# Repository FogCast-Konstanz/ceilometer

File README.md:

# Fogcast ceilometer

Fogcast is an experimental laser ceilometer intended to measure atmospheric
backscatter and, eventually, cloud-base height. This repository contains the
instrument electronics and mechanical designs, Pico 2 firmware, board bring-up
interface, and Raspberry Pi acquisition and dashboard software.

The instrument uses pseudo-randomly modulated continuous-wave lidar (PRN-CW).
A laser transmits a repeating binary sequence. A silicon photomultiplier (SiPM)
receiver detects returned photons, and correlation with the transmitted sequence
produces a backscatter profile versus range.

## Project status

The project currently supports board commissioning, receiver characterization,
PRN acquisition, raw-data recording and range-profile display. It is a research
prototype: calibrated atmospheric ranging and automatic cloud-base detection
have not been established. Displayed profiles require timing, optical and
calibration validation before they can be interpreted as qualified measurements.

The firmware currently operates at **500 MHz with a requested 1.5 V core supply**,
above the Pico 2's rated clock. This configuration has been used in bench tests;
stability must be checked on each instrument. See the
[clock and watchdog notes](docs/bringup/operating-clock.md) for evidence and limits.

## Instrument architecture

- **Pico 2 / RP2350:** generates PRN modulation, counts receiver pulses, captures
  counter snapshots through DMA, accumulates histograms, and controls peripherals.
- **Transmitter:** laser-current DAC and driver, plus a TEC regulated from a
  DS18B20 laser-temperature sensor.
- **Receiver:** SiPM bias control, receiver-temperature feedback and an adjustable
  comparator threshold. Bias targets track temperature and are limited to 50 V;
  this software limit is not a measured-voltage hardware clamp.
- **Raspberry Pi:** supervises measurements over USB CDC, records raw histograms,
  calculates correlation profiles and serves the instrument dashboard.

Acquisition runs on one Pico core in finite bursts. A common hardware event
starts transmission and receiver sampling. Startup periods are discarded after
each restart, and sensor servicing occurs between bursts. The nominal one-second
integration refers to accepted exposure; elapsed time is longer because of
warmup and processing gaps. Both are recorded separately.

See [acquisition architecture](docs/architecture/continuous-acquisition.md) and
[USB protocol](interfaces/usb-protocol.md) for the implementation details.

## Explore without hardware

Requirements: Python 3.10 or newer. Run these commands from the repository root:

```sh
python -m venv .venv
# Linux / Raspberry Pi:
. .venv/bin/activate
# Windows PowerShell alternative: .venv\Scripts\Activate.ps1
python -m pip install -e software/instrument
ceilometer-dashboard --demo --http-port 8081
```

Open **http://127.0.0.1:8081/**. Demo mode uses simulated data and does not open
USB or control physical outputs.

If you need the binary CAD, print projects or other large design assets, install
Git LFS and run `git lfs pull` after cloning.

## Connect an instrument

1. Assemble and inspect the hardware against the
   [electronics sources](hardware/electronics/README.md). Review the
   [bring-up documentation](docs/bringup) and [laser safety material](docs/safety)
   before applying power or commissioning optical output.
2. Build and load the Pico firmware as described below. USB powers the Pico;
   the instrument's other circuits require their designed external supplies.
3. Open [software/bringup/index.html](software/bringup/index.html) directly in
   desktop Chrome or Edge. Connect through Web Serial to inspect sensors,
   configure parameters and commission each functional block. Confirm wiring,
   TEC polarity, temperature feedback, DAC limits and board-specific calibration.
4. Disconnect the bring-up GUI before starting the Pi application. Only one
   program should own the instrument's USB connection.
5. Start the instrument dashboard in the Python environment:

```sh
ceilometer-dashboard auto --http-port 8080 --output measurements
```

Open **http://127.0.0.1:8080/**. Automatic discovery selects only USB manufacturer
`Fogcast`, product `Fogcast Ceilometer`, with the expected Pico VID/PID. Other
Picos are ignored; multiple matching ceilometers require an explicit device
path. Firmware 0.6.4 or newer supplies this USB identity.

The application starts **disabled**. Select a measurement mode and press
**Enable instrument** explicitly. **Disable for servicing** requests shutdown
and reports whether the board has acknowledged the laser, bias and TEC off.
External supplies remain powered. Temperature, driver-fault, watchdog and USB
lease interlocks remain active; reconnecting does not resume measurement.

For access from another computer on a trusted network or VPN:

```sh
export CEILOMETER_WEB_TOKEN="$(python -c 'import secrets; print(secrets.token_urlsafe(32))')"
ceilometer-dashboard auto --listen 0.0.0.0 --http-port 8080 --output measurements
```

Open `http://<pi-address>:8080/` and enter the token. Network binding requires a
token of at least 24 characters. The supplied server uses HTTP; use an HTTPS
reverse proxy where transport encryption is required. Keep tokens and local
configuration outside Git.

## Build firmware and run checks

Firmware requirements: Pico SDK **2.3.0**, a compatible Arm GNU toolchain, CMake
and a supported build tool. Set the SDK path for your machine:

```sh
cmake -S firmware/pico2 -B build/firmware -DPICO_BOARD=pico2 -DPICO_SDK_PATH=/path/to/pico-sdk
cmake --build build/firmware
```

The output is `build/firmware/ceilometer.uf2`. To load it manually, hold BOOTSEL
while connecting the Pico and copy the UF2 to its bootloader drive. Select the
intended board carefully when several Picos are connected.

Power-driver build flags default **OFF**. Commissioned hardware requires the
appropriate `CEIL_ENABLE_LASER`, `CEIL_ENABLE_BIAS` and `CEIL_ENABLE_TEC` options,
as well as a calibrated `CEIL_BIAS_MAX_CODE`. Build permission alone does not
turn outputs on. Do not reuse another board's DAC calibration or limits without
verification; see [SiPM bias control](docs/bringup/sipm-bias.md) and
[temperature control](docs/bringup/temperature-control.md).

Portable regression checks require a native C compiler; install the instrument
Python dependencies first. Node.js 22 or newer enables the GUI protocol checks.

```sh
cmake -S firmware/pico2 -B build/host -DCEIL_HOST_TESTS=ON
cmake --build build/host
ctest --test-dir build/host --output-on-failure
python scripts/check_design_sources.py
```

After editing the bring-up GUI, regenerate its direct-open bundle with
`python software/bringup/build_bundle.py`. After changing firmware parameter or
telemetry inventories, first run `python software/bringup/update_metadata.py`.

## Repository guide

| Directory | Contents |
|---|---|
| [firmware/pico2](firmware/pico2) | C/PIO firmware, peripheral drivers and firmware tests |
| [software/bringup](software/bringup) | Direct-open HTML/Web Serial commissioning GUI |
| [software/instrument](software/instrument) | Python package, recorder, processing and Pi dashboard |
| [hardware/electronics](hardware/electronics) | KiCad projects, custom libraries and LTspice simulations |
| [hardware/mechanical](hardware/mechanical) | CAD exchange files, meshes, drawings, print projects and studies |
| [interfaces](interfaces) | USB protocol and recorded-data format |
| [analysis](analysis) | Bench datasets, calibration evidence and plotting scripts |
| [docs](docs) | Architecture, bring-up, operation and safety documentation |
| [deploy](deploy) | Pi service templates, release packaging, updates and rollback |

Live measurements and generated build outputs are not versioned. Small recorded
bench datasets are retained as engineering evidence; see the
[measurement format](interfaces/measurement-format.md) for data interpretation.

## Deployment

After building the firmware, create a checksummed runtime release:

```sh
python deploy/releases/package_release.py --output build/ceilometer-release.tar.gz
```

The archive contains the Pi application, deployment tools, interface documents
and UF2. It excludes CAD, credentials and live measurements. Service templates
are under `deploy/raspberry-pi/`; install/update tools are under `deploy/releases/`.
Automated updates require an explicitly configured Git repository and target
Pico serial number. Updates are applied only while outputs are confirmed off,
and the service restarts disabled. Hardware-only commits do not trigger the
firmware deployment workflow.

### Pi-initiated continuous deployment

GitHub Actions builds and tests a release, then publishes it to the repository's
`deploy` branch. **GitHub never connects to the Raspberry Pi.** A systemd timer
on the Pi initiates an outbound Git fetch every five minutes (with up to 30 s
jitter), starting about two minutes after boot. No inbound port, webhook,
public Pi address or university firewall exception is needed. The Pi needs
outbound HTTPS access to the Git server; configure its proxy if required.

After provisioning the instrument release under `/opt/ceilometer-firmware`,
install and configure the poller on the Pi:

```sh
sudo install -d -m 0750 /etc/ceilometer
sudo install -m 0600 /opt/ceilometer-firmware/deploy/raspberry-pi/cd.env.example /etc/ceilometer/cd.env
sudoedit /etc/ceilometer/cd.env
# Set the HTTPS repository URL, refs/heads/deploy and the target Pico USB serial.
sudo install -m 0644 /opt/ceilometer-firmware/deploy/raspberry-pi/ceilometer-update.service /etc/systemd/system/
sudo install -m 0644 /opt/ceilometer-firmware/deploy/raspberry-pi/ceilometer-update.timer /etc/systemd/system/
sudo systemctl daemon-reload
sudo systemctl enable --now ceilometer-update.timer
```

For a private repository, configure read-only Git credentials on the Pi for the
root-run updater. Do not embed credentials in the URL or commit them. GitHub
Actions needs permission to publish the deployment branch, but no Pi credentials.

```sh
systemctl list-timers ceilometer-update.timer
journalctl -u ceilometer-update.service -n 50
# Trigger an immediate check:
sudo systemctl start ceilometer-update.service
```

While measuring, or when shutdown cannot be confirmed, the updater defers the
update until a later poll. Network outages leave the installed release running;
the next scheduled poll retries. The installer verifies release hashes, targets
the configured Pico, checks the restarted service and attempts rollback on failure.
Neither polling nor an update automatically enables measurements. An initial
local installation is required before polling can update the Pi itself.

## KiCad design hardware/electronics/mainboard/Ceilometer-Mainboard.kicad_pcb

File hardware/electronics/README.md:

# Electronics sources

`mainboard` preserves the complete KiCad project, A/B board variants, custom
symbols/footprints, 3D models and project-local library tables. No board variant
was silently selected or deleted. `simulations` contains LTspice source studies.
`reference` contains historical firmware-review netlist/hash exports; the KiCad
sources are authoritative and those exports may describe earlier revisions.

`history/kicad-local-history.bundle` preserves all Git refs from KiCad local
history. Inspect separately with `git clone <bundle> <temporary-directory>`;
do not unpack it as a nested live repository. Automatic backups, lock files,
local editor preferences and cached Python files are excluded from the import.

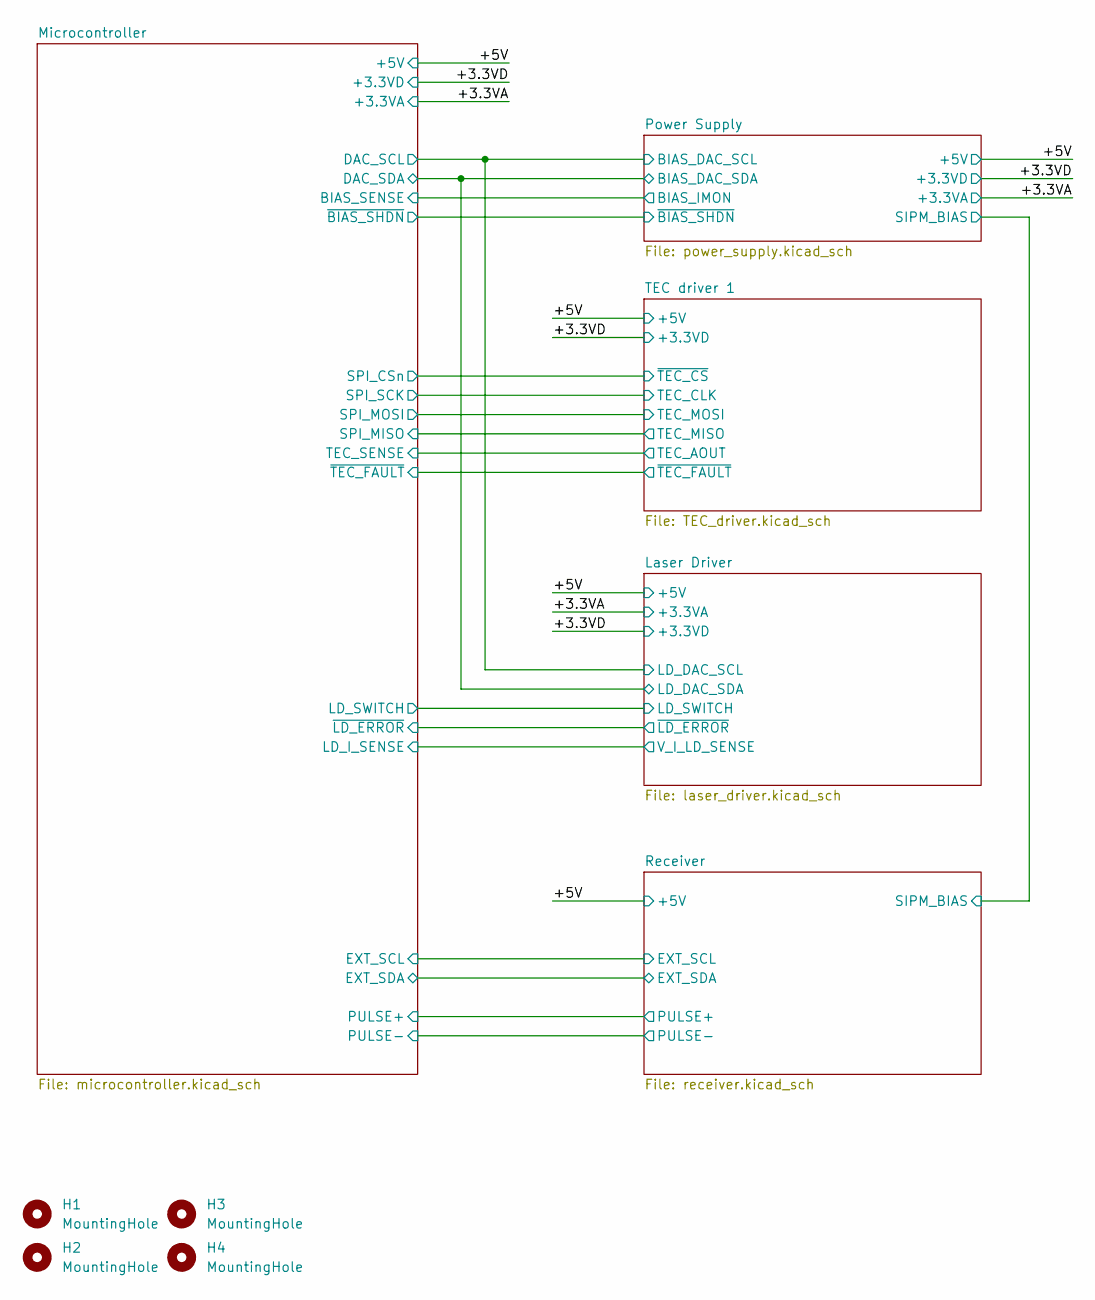
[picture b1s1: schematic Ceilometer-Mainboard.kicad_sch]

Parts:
H1, H2, H3, H4: MountingHole; MountingHole_2.5mm

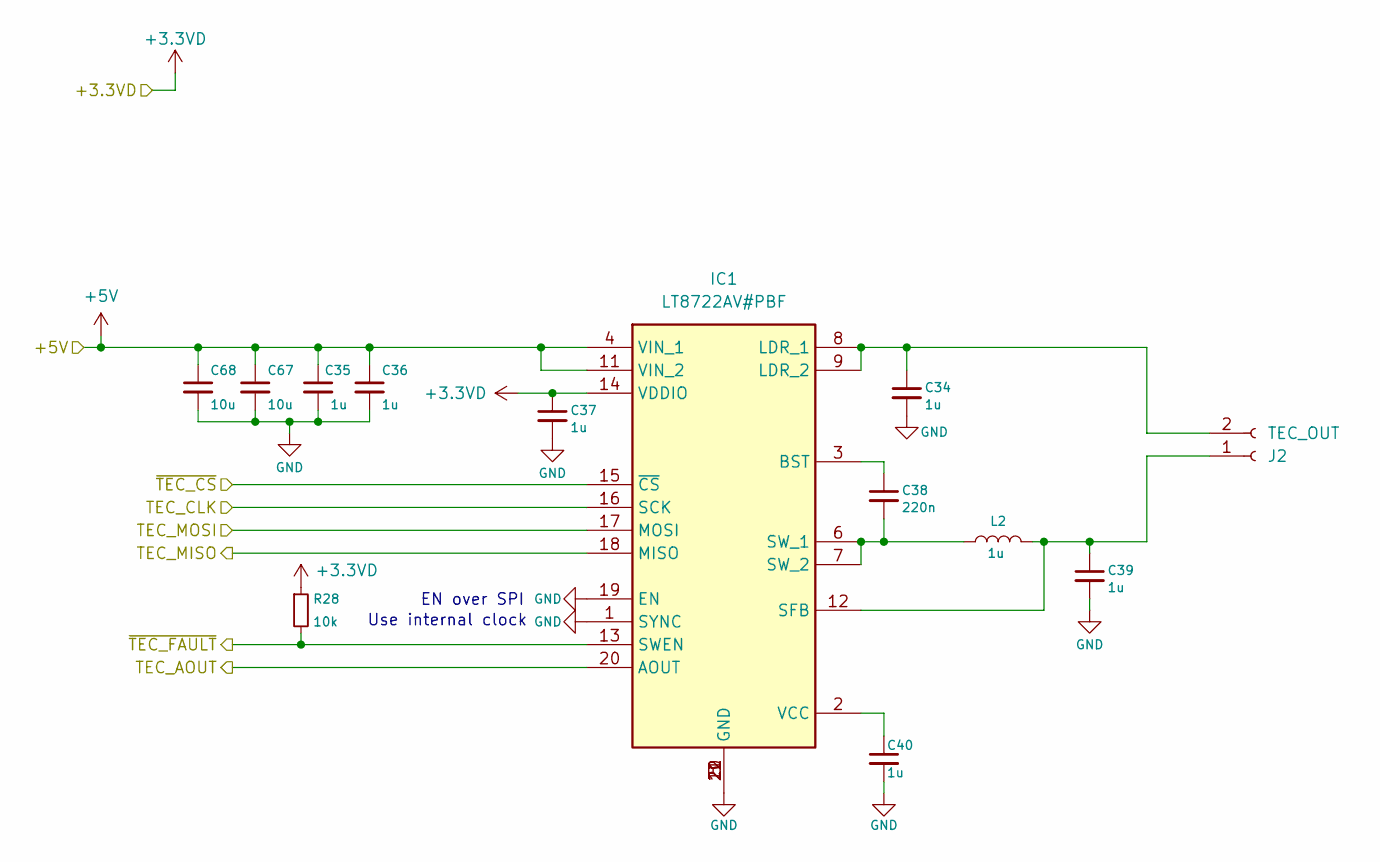
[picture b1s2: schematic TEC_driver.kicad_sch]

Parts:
C34, C35, C36, C37, C39, C40: 1u; C_0402_1005Metric; Voltage 35V; MPN C1005X5R1V105K050BE
C38: 220n; C_0402_1005Metric; Voltage 63V; MPN GRM155R61J224ME01J
C67, C68: 10u; C_0805_2012Metric; Voltage 50V; PartNumber GRM21BR61H106KE43K
IC1: LT8722AV#PBF; LT8722AVPBF; Mouser Part Number 584-LT8722AVPBF
J2: TEC_OUT; Molex_Pico-EZmate_78171-0002_1x02-1MP_P1.20mm_Vertical
L2: 1u; L_Wurth_WE-PMFI-252012; MPN 74479325207210
R28: 10k; R_0402_1005Metric; MPN ERA-2AEB103X

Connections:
+3.3VD: C37.1, IC1.14 (VDDIO), R28.1; also elsewhere on the board
+5V: C35.1, C36.1, C67.1, C68.1, IC1.4 (VIN_1), IC1.11 (VIN_2); also elsewhere on the board
/Microcontroller/SPI_CSn: IC1.15 (~CS); also elsewhere on the board
/Microcontroller/SPI_MISO: IC1.18 (MISO); also elsewhere on the board
/Microcontroller/SPI_MOSI: IC1.17 (MOSI); also elsewhere on the board
/Microcontroller/SPI_SCK: IC1.16 (SCK); also elsewhere on the board
/Microcontroller/TEC_SENSE: IC1.20 (AOUT); also elsewhere on the board
/Microcontroller/~TEC_FAULT: IC1.13 (SWEN), R28.2; also elsewhere on the board
GND: C34.2, C35.2, C36.2, C37.2, C39.2, C40.2, C67.2, C68.2, IC1.1 (SYNC), IC1.5 (GND), IC1.10 (GND), IC1.19 (EN), IC1.21 (GND), IC1.22 (GND); also elsewhere on the board
unnamed: C38.1, IC1.3 (BST)
unnamed: C34.1, IC1.8 (LDR_1), IC1.9 (LDR_2), J2.2
unnamed: C39.1, IC1.12 (SFB), J2.1, L2.2
unnamed: C38.2, IC1.6 (SW_1), IC1.7 (SW_2), L2.1
unnamed: C40.1, IC1.2 (VCC)

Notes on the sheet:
EN over SPI
Use internal clock

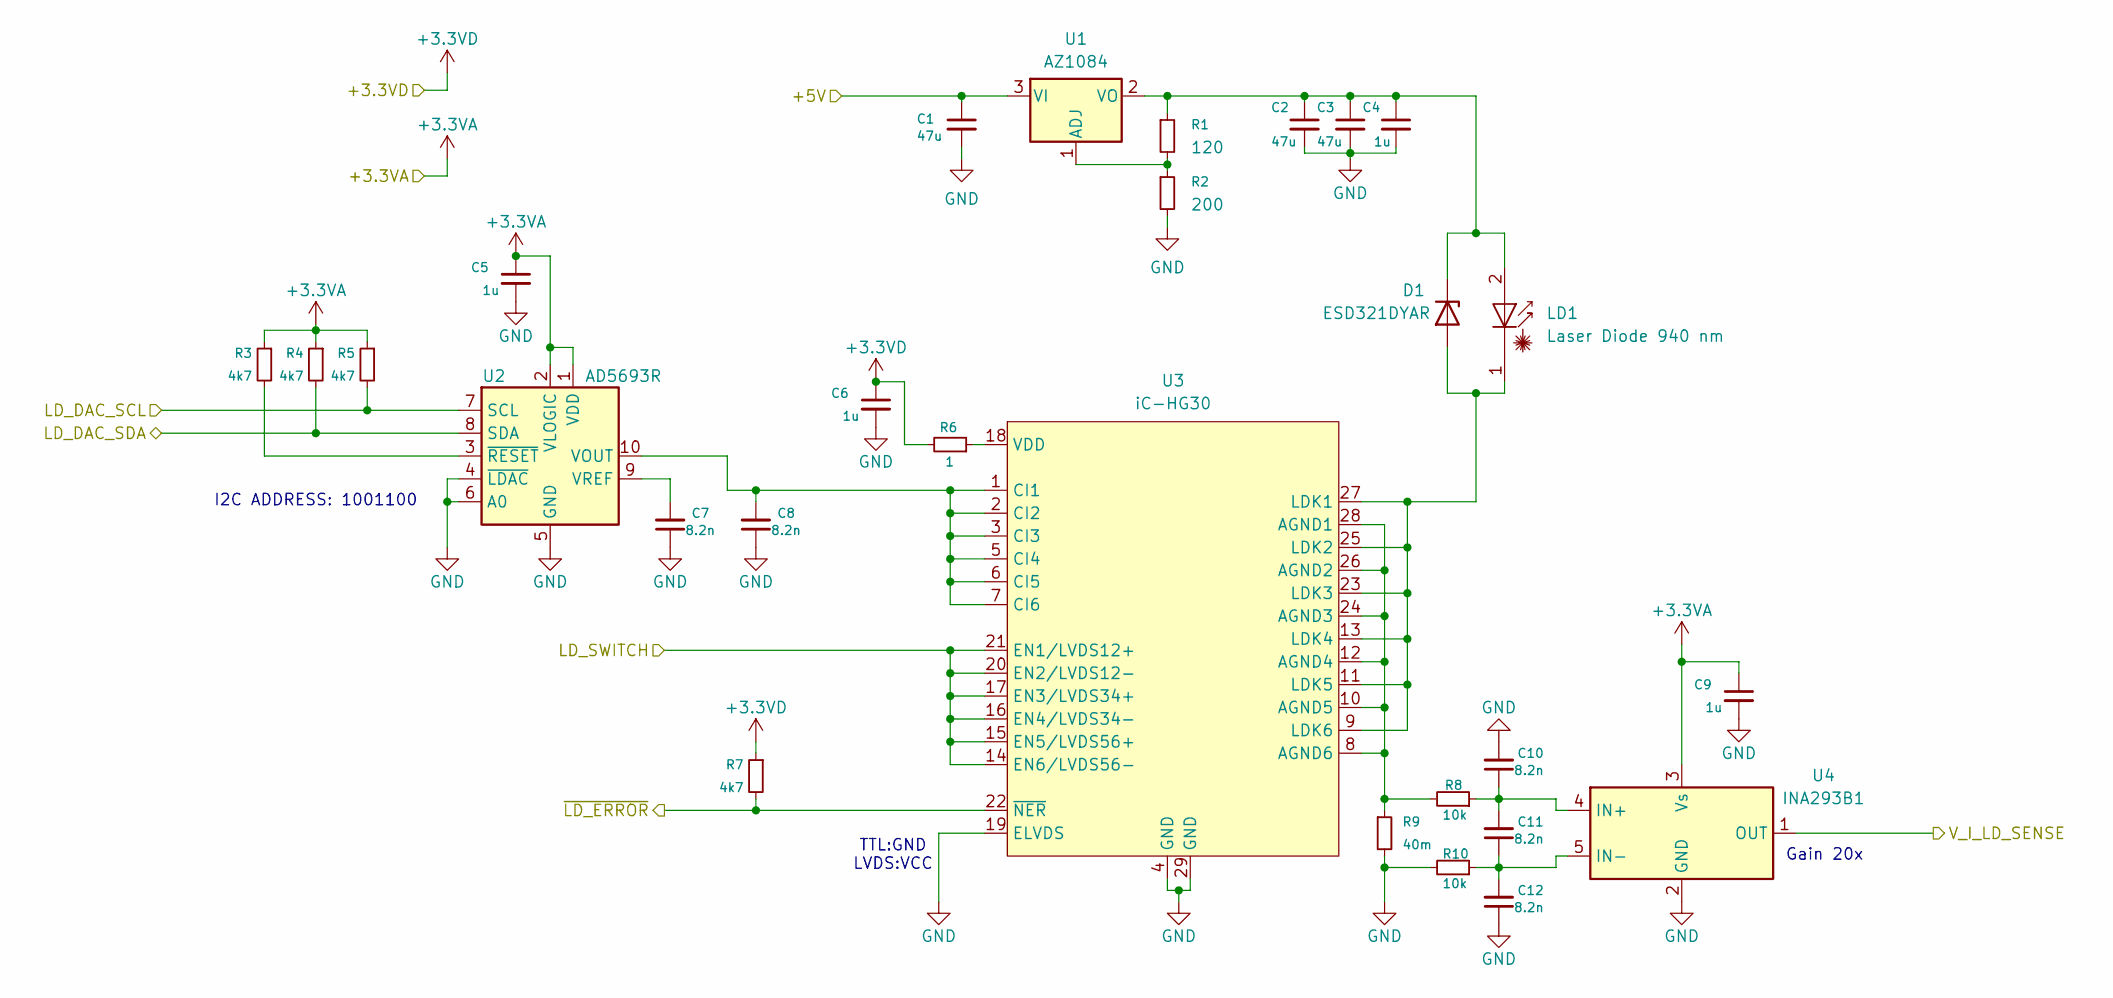
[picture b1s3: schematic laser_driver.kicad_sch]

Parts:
C1, C2, C3: 47u; C_0805_2012Metric; Voltage 10V; MPN LMK212BBJ476MG-T
C4, C5, C6, C9: 1u; C_0402_1005Metric; Voltage 35V; MPN C1005X5R1V105K050BE
C7, C8, C10, C11, C12: 8.2n; C_0402_1005Metric; Voltage 50V; MPN GRM1555C1H822JE01D
D1: ESD321DYAR; D_SOD-523; MPN ESD321DYAR
LD1: Laser Diode 940 nm; Molex_Pico-EZmate_78171-0002_1x02-1MP_P1.20mm_Vertical; MPN 781710002
R1: 120; R_0402_1005Metric; MPN ERA-2AEB121X
R2: 200; R_0402_1005Metric; MPN ERA-2AED201X
R3, R4, R5, R7: 4k7; R_0402_1005Metric; MPN ERA-2AED472X
R6: 1; R_0402_1005Metric; MPN CRCW04021R00FKED
R8, R10: 10k; R_0402_1005Metric; MPN ERA-2AEB103X
R9: 40m; R_0603_1608Metric; MPN PE0603DRF570R04L
U1: AZ1084; TO-263-2; MPN AZ1084CD-ADJTRG1
U2: AD5693R; MSOP-10_3x3mm_P0.5mm; MPN AD5693RARMZ-RL7
U3: iC-HG30; QFN-28-1EP_5x5mm_P0.5mm_EP3.1x3.15mm_ThermalVias; MPN iC-HG30
U4: INA293B1; SOT-23-5; MPN INA293B1IDBVR

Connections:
+3.3VA: C5.1, C9.1, R3.1, R4.1, R5.1, U2.1 (VDD), U2.2 (VLOGIC), U4.3 (Vs); also elsewhere on the board
+3.3VD: C6.1, R6.2, R7.1; also elsewhere on the board
+5V: C1.1, U1.3 (VI); also elsewhere on the board
/Laser Driver/LD_DAC_SCL: R5.2, U2.7 (SCL); also elsewhere on the board
/Laser Driver/LD_DAC_SDA: R4.2, U2.8 (SDA); also elsewhere on the board
/Laser Driver/LD_SWITCH: U3.14 (EN6/LVDS56-), U3.15 (EN5/LVDS56+), U3.16 (EN4/LVDS34-), U3.17 (EN3/LVDS34+), U3.20 (EN2/LVDS12-), U3.21 (EN1/LVDS12+); also elsewhere on the board
/Laser Driver/V_I_LD_SENSE: U4.1 (OUT); also elsewhere on the board
/Laser Driver/~LD_ERROR: R7.2, U3.22 (~NER); also elsewhere on the board
GND: C1.2, C2.2, C3.2, C4.2, C5.2, C6.2, C7.1, C8.1, C9.2, C10.2, C12.1, R2.2, R9.2, R10.2, U2.4 (~LDAC), U2.5 (GND), U2.6 (A0), U3.4 (GND), U3.19 (ELVDS), U3.29 (GND), U4.2 (GND); also elsewhere on the board
unnamed: D1.2 (A), LD1.1 (K), U3.9 (LDK6), U3.11 (LDK5), U3.13 (LDK4), U3.23 (LDK3), U3.25 (LDK2), U3.27 (LDK1)
unnamed: C2.1, C3.1, C4.1, D1.1 (K), LD1.2 (A), R1.1, U1.2 (VO)
unnamed: R1.2, R2.1, U1.1 (ADJ)
unnamed: C8.2, U2.10 (VOUT), U3.1 (CI1), U3.2 (CI2), U3.3 (CI3), U3.5 (CI4), U3.6 (CI5), U3.7 (CI6)
unnamed: C7.2, U2.9 (VREF)
unnamed: R3.2, U2.3 (~RESET)
unnamed: R8.2, R9.1, U3.8 (AGND6), U3.10 (AGND5), U3.12 (AGND4), U3.24 (AGND3), U3.26 (AGND2), U3.28 (AGND1)
unnamed: R6.1, U3.18 (VDD)
unnamed: C10.1, C11.2, R8.1, U4.4 (IN+)
unnamed: C11.1, C12.2, R10.1, U4.5 (IN-)

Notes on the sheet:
I2C ADDRESS: 1001100
TTL:GND LVDS:VCC
Gain 20x

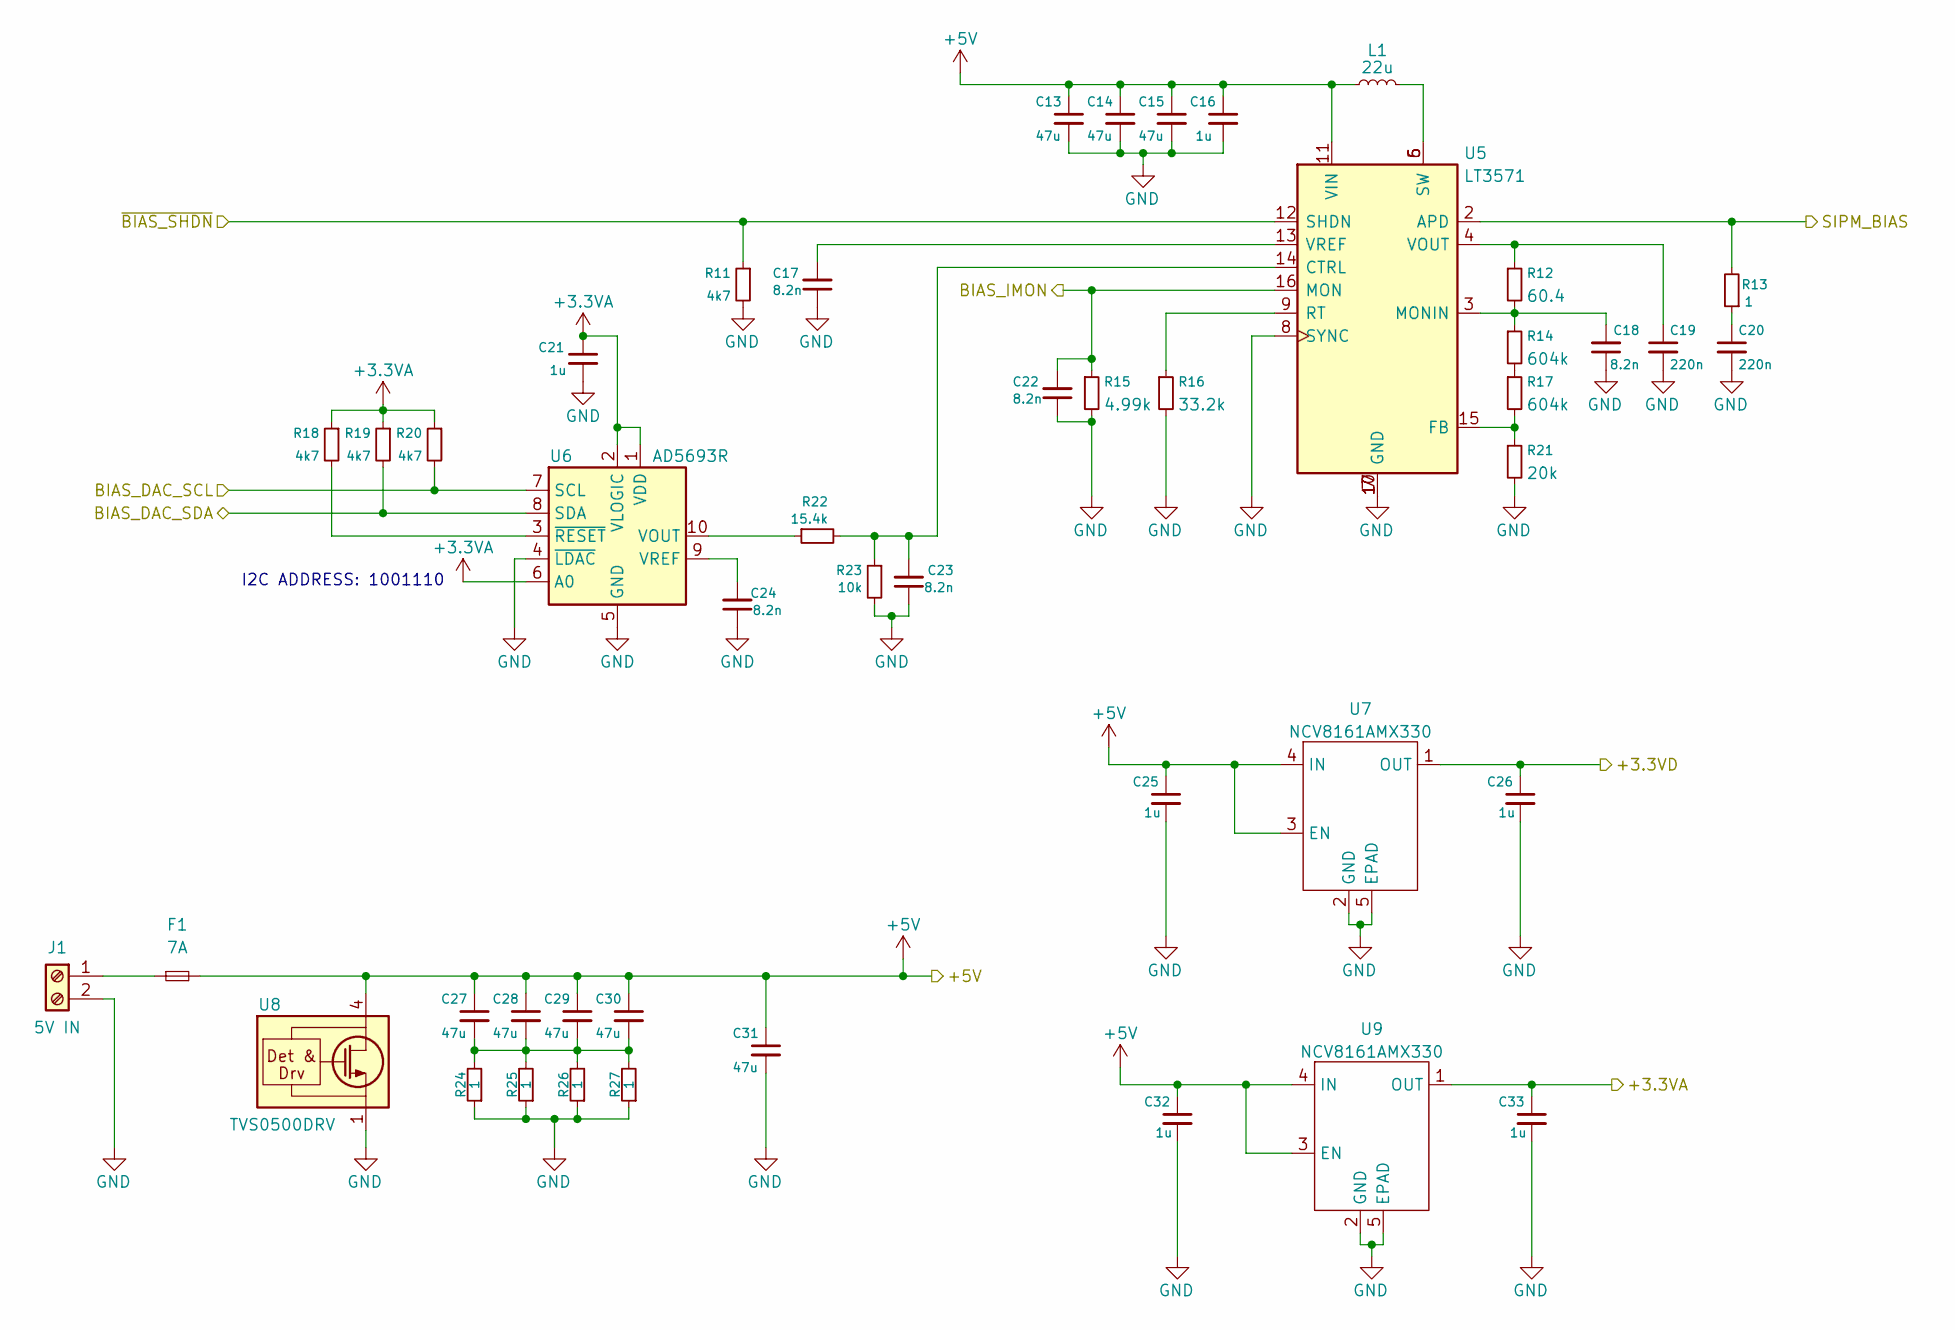
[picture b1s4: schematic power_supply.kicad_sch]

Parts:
C13, C14, C15, C27, C28, C29, C30, C31: 47u; C_0805_2012Metric; Voltage 10V; MPN LMK212BBJ476MG-T
C16, C21, C25, C26, C32, C33: 1u; C_0402_1005Metric; Voltage 35V; MPN C1005X5R1V105K050BE
C17, C18, C22, C23, C24: 8.2n; C_0402_1005Metric; Voltage 50V; MPN GRM1555C1H822JE01D
C19, C20: 220n; C_0402_1005Metric; Voltage 63V; MPN GRM155R61J224ME01J
F1: 7A; Fuseholder_Littelfuse_Nano2_154x; MPN 0154007.DRT
J1: 5V IN; TerminalBlock_RND_205-00001_1x02_P5.00mm_Horizontal
L1: 22u; L_Abracon_ASPI-4030S; MPN ASPI-4030S-220M-T
R11, R18, R19, R20: 4k7; R_0402_1005Metric; MPN ERA-2AED472X
R12: 60.4; R_0402_1005Metric; MPN RG1005P-60R4-D-T10
R13, R24, R25, R26, R27: 1; R_0402_1005Metric; MPN CRCW04021R00FKED
R14, R17: 604k; R_0402_1005Metric; MPN CR0402-FX-6043GLF
R15: 4.99k; R_0402_1005Metric; MPN RT0402BRD074K99L
R16: 33.2k; R_0402_1005Metric; MPN RT0402BRD0733K2L
R21: 20k; R_0402_1005Metric; MPN ERA-2AED203X
R22: 15.4k; R_0402_1005Metric; Tolerance 0.1; MPN RT0402BRD0715K4L
R23: 10k; R_0402_1005Metric; MPN ERA-2AEB103X
U5: LT3571; QFN-16-1EP_3x3mm_P0.5mm_EP1.45x1.45mm_ThermalVias; MPN LT3571EUD#PBF
U6: AD5693R; MSOP-10_3x3mm_P0.5mm; MPN AD5693RARMZ-RL7
U7, U9: NCV8161AMX330; Texas_XDFN-4_1x1mm_P0.65mm; MPN NCV8161AMX330TBG
U8: TVS0500DRV; WSON-6-1EP_2x2mm_P0.65mm_EP1x1.6mm; MPN TVS0500DRV

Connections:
+3.3VA: C21.1, C33.1, R18.1, R19.1, R20.1, U6.1 (VDD), U6.2 (VLOGIC), U6.6 (A0), U9.1 (OUT); also elsewhere on the board
+3.3VD: C26.1, U7.1 (OUT); also elsewhere on the board
+5V: C13.1, C14.1, C15.1, C16.1, C25.1, C27.1, C28.1, C29.1, C30.1, C31.1, C32.1, F1.2, L1.1, U5.11 (VIN), U7.3 (EN), U7.4 (IN), U8.4 (IN), U8.5 (IN), U8.6 (IN), U9.3 (EN), U9.4 (IN); also elsewhere on the board
/Laser Driver/LD_DAC_SCL: R20.2, U6.7 (SCL); also elsewhere on the board
/Laser Driver/LD_DAC_SDA: R19.2, U6.8 (SDA); also elsewhere on the board
/Microcontroller/BIAS_SENSE: C22.2, R15.1, U5.16 (MON); also elsewhere on the board
/Microcontroller/~BIAS_SHDN: R11.1, U5.12 (SHDN); also elsewhere on the board
/Power Supply/SIPM_BIAS: R13.2, U5.2 (APD); also elsewhere on the board
GND: C13.2, C14.2, C15.2, C16.2, C17.1, C18.1, C19.2, C20.2, C21.2, C22.1, C23.1, C24.1, C25.2, C26.2, C31.2, C32.2, C33.2, J1.2, R11.2, R15.2, R16.2, R21.2, R23.2, R24.1, R25.1, R26.1, R27.1, U5.7 (GND), U5.8 (SYNC), U5.10 (GND), U5.17 (GND), U6.4 (~LDAC), U6.5 (GND), U7.2 (GND), U7.5 (EPAD), U8.1 (GND), U8.2 (GND), U8.3 (GND), U8.7 (GND), U9.2 (GND), U9.5 (EPAD); also elsewhere on the board
unnamed: C20.1, R13.1
unnamed: C27.2, C28.2, C29.2, C30.2, R24.2, R25.2, R26.2, R27.2
unnamed: F1.1, J1.1
unnamed: L1.2, U5.5 (SW), U5.6 (SW)
unnamed: R14.2, R17.1
unnamed: C23.2, R22.2, R23.1, U5.14 (CTRL)
unnamed: R17.2, R21.1, U5.15 (FB)
unnamed: C18.2, R12.2, R14.1, U5.3 (MONIN)
unnamed: R16.1, U5.9 (RT)
unnamed: C19.1, R12.1, U5.4 (VOUT)
unnamed: C17.2, U5.13 (VREF)
unnamed: R22.1, U6.10 (VOUT)
unnamed: C24.2, U6.9 (VREF)
unnamed: R18.2, U6.3 (~RESET)

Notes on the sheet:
I2C ADDRESS: 1001110

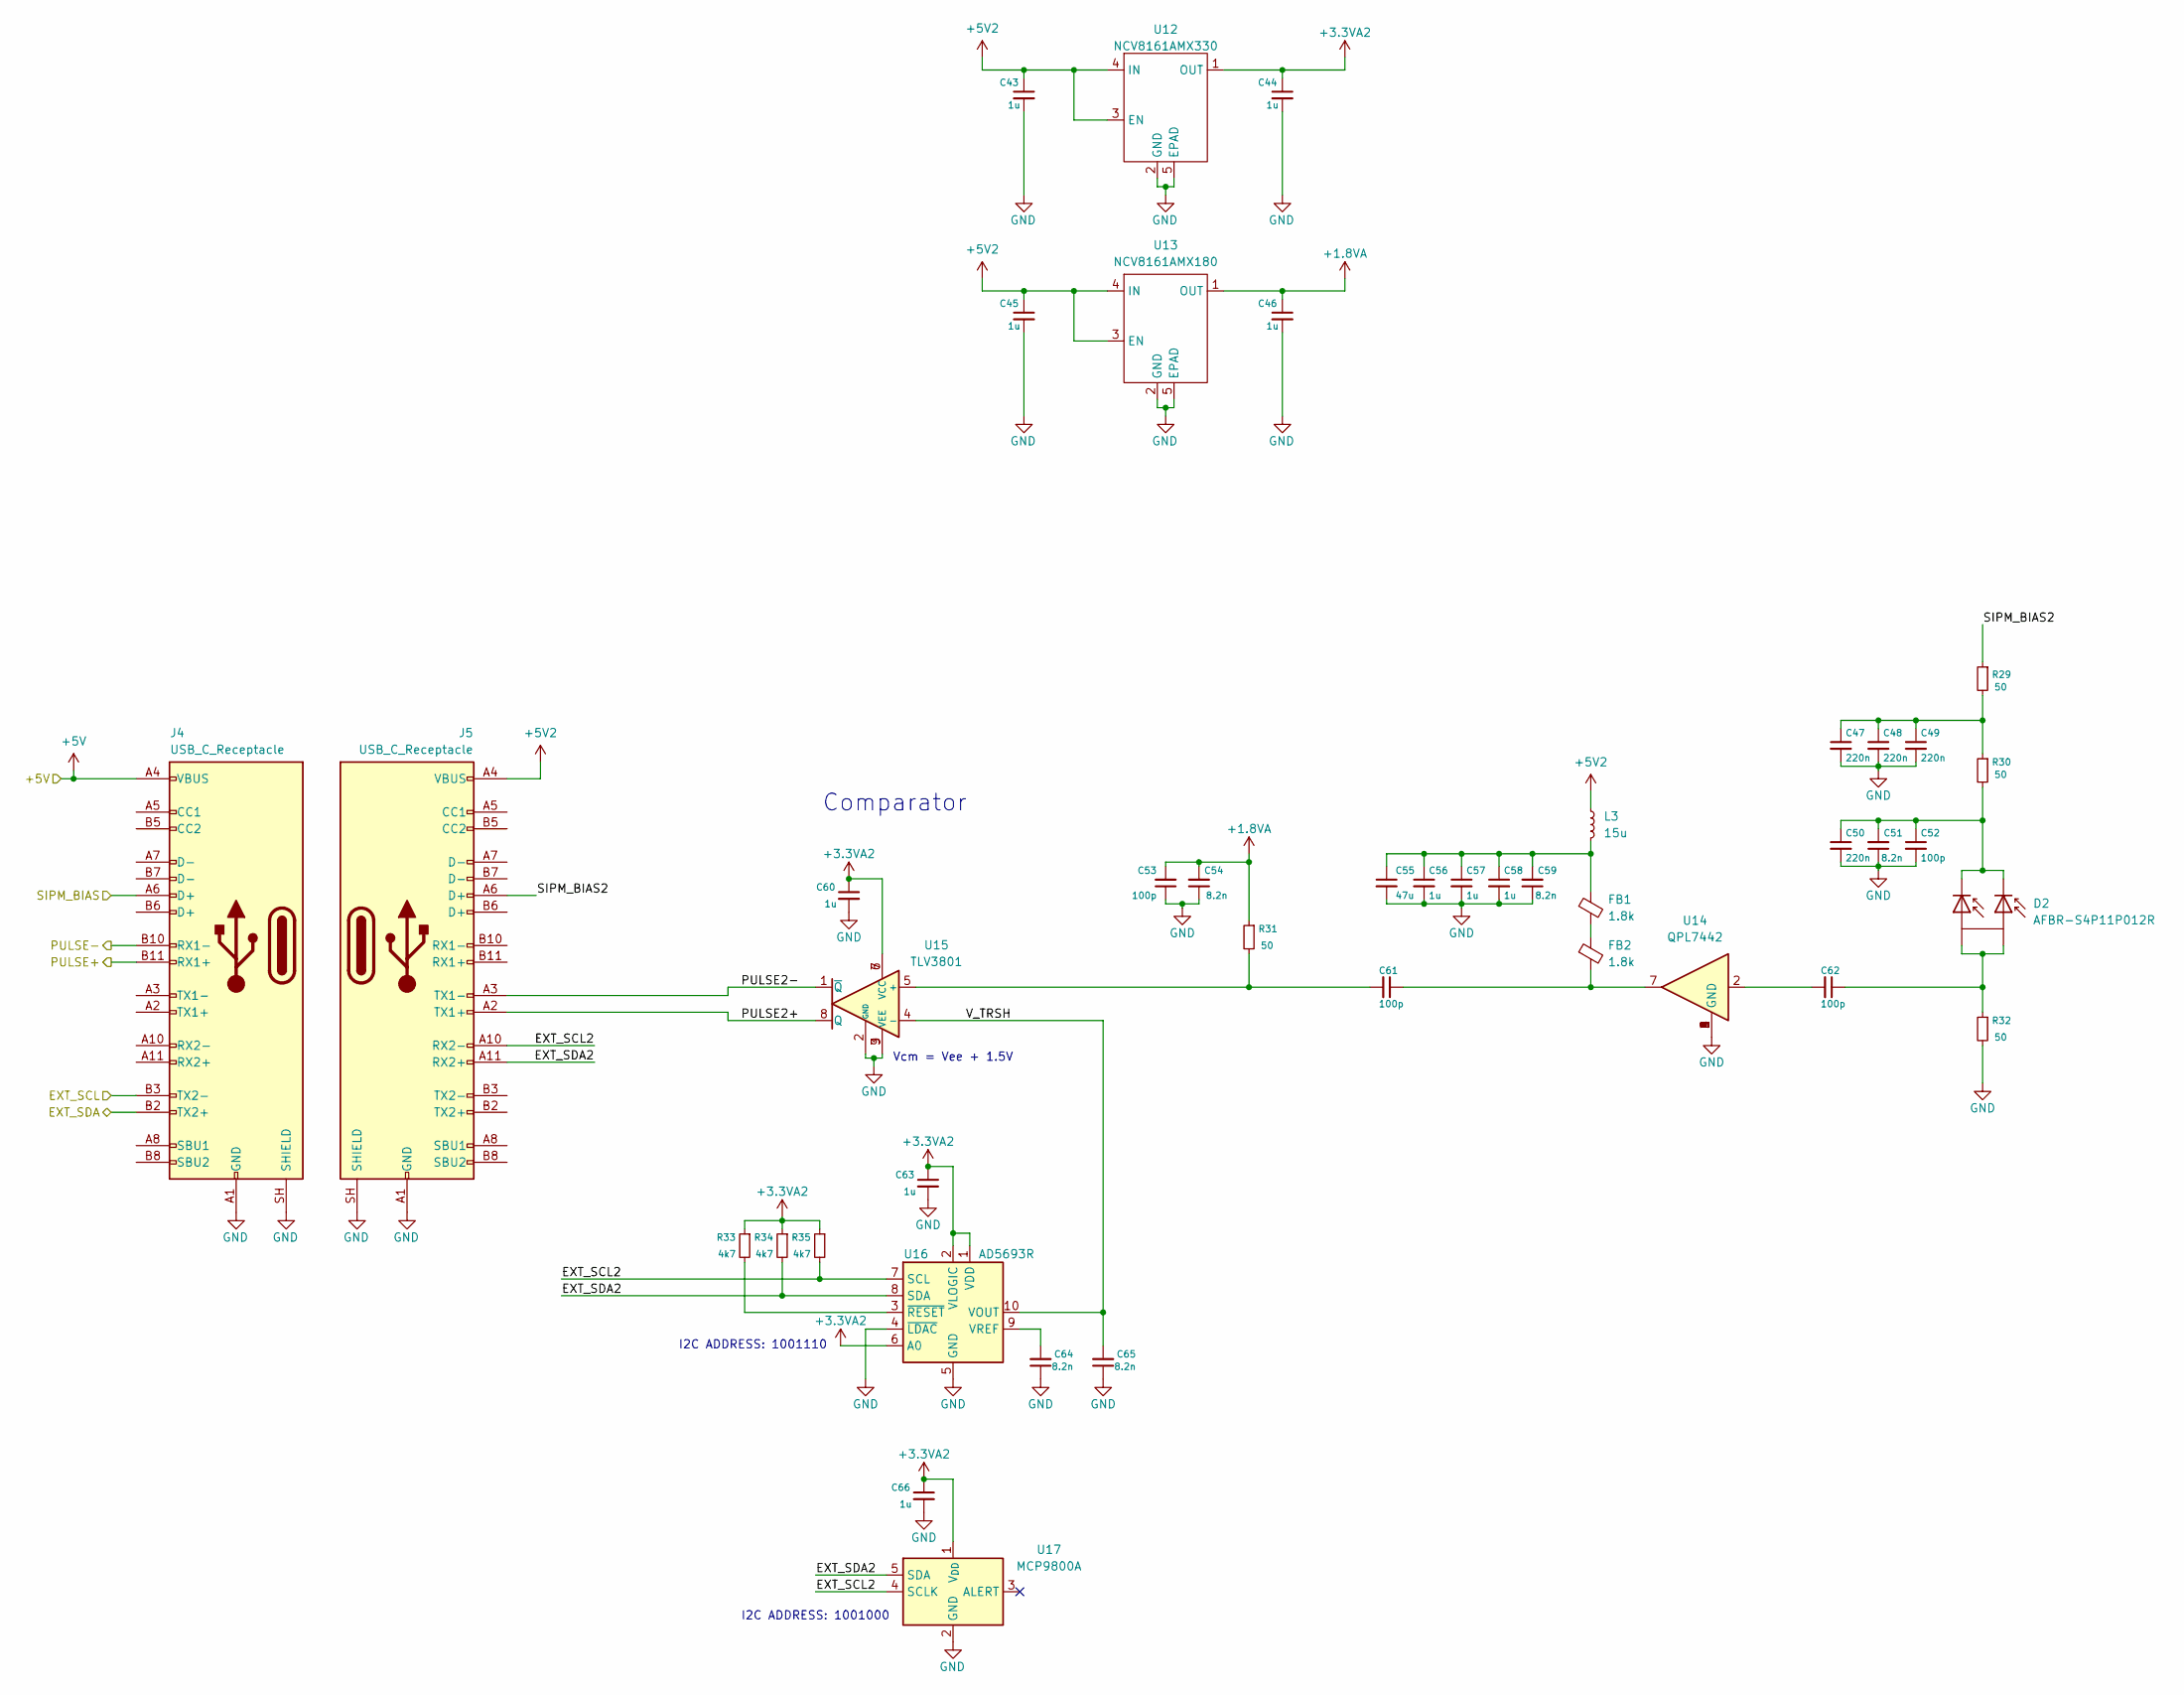
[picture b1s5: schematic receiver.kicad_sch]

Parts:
C43, C44, C45, C46, C56, C57, C58, C60, C63, C66: 1u; C_0402_1005Metric; Voltage 35V; MPN C1005X5R1V105K050BE
C47, C48, C49, C50: 220n; C_0402_1005Metric; Voltage 63V; MPN GRM155R61J224ME01J
C51, C54, C59, C64, C65: 8.2n; C_0402_1005Metric; Voltage 50V; MPN GRM1555C1H822JE01D
C52, C53: 100p; C_0402_1005Metric; Voltage 50V; MPN RF15N101J500CT
C55: 47u; C_0805_2012Metric; Voltage 10V; MPN LMK212BBJ476MG-T
C61, C62: 100p; C_0201_0603Metric; Voltage 25V; MPN CC0201JPNPO8BN101
D2: AFBR-S4P11P012R; Broadcom_AFBR-S4P11P012R; MPN AFBR-S4P11P012R
FB1, FB2: 1.8k; L_0402_1005Metric; MPN MMZ1005A182ET000
J4, J5: USB_C_Receptacle; USB_C_Receptacle_Amphenol_12401610E4-2A; MPN 12401610E4#2A
L3: 15u; PFL4514; MPN PFL4514-153MEC
R29, R30: 50; R_0402_1005Metric; MPN TNPW040250R0BEED
R31, R32: 50; R_0201_0603Metric; MPN TNPW020150R0DEED
R33, R34, R35: 4k7; R_0402_1005Metric; MPN ERA-2AED472X
U12: NCV8161AMX330; Texas_XDFN-4_1x1mm_P0.65mm; MPN NCV8161AMX330TBG
U13: NCV8161AMX180; Texas_XDFN-4_1x1mm_P0.65mm; MPN NCV8161AMX330TBG
U14: QPL7442; DFN-8-1EP_2x2mm_P0.5mm_EP0.8x1.6mm; MPN QPL7442
U15: TLV3801; TLV3801DSGR; MPN TLV3801DSGR
U16: AD5693R; MSOP-10_3x3mm_P0.5mm; MPN AD5693RARMZ-RL7
U17: MCP9800A; SOT-23-5; MPN MCP9800A0T-M/OT

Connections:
+1.8VA: C46.1, C53.2, C54.2, R31.1, U13.1 (OUT)
+3.3VA2: C44.1, C60.1, C63.1, C66.1, R33.1, R34.1, R35.1, U12.1 (OUT), U15.6 (VCC), U15.7 (VCC), U16.1 (VDD), U16.2 (VLOGIC), U16.6 (A0), U17.1 (V_{DD})
+5V: J4.A4 (VBUS), J4.A9 (VBUS), J4.B4 (VBUS), J4.B9 (VBUS); also elsewhere on the board
+5V2: C43.1, C45.1, J5.A4 (VBUS), J5.A9 (VBUS), J5.B4 (VBUS), J5.B9 (VBUS), L3.1, U12.3 (EN), U12.4 (IN), U13.3 (EN), U13.4 (IN)
/Microcontroller/EXT_SCL: J4.B3 (TX2-); also elsewhere on the board
/Microcontroller/EXT_SDA: J4.B2 (TX2+); also elsewhere on the board
/Microcontroller/PULSE+: J4.B11 (RX1+); also elsewhere on the board
/Microcontroller/PULSE-: J4.B10 (RX1-); also elsewhere on the board
/Power Supply/SIPM_BIAS: J4.A6 (D+); also elsewhere on the board
/Receiver/EXT_SCL2: J5.A10 (RX2-), R35.2, U16.7 (SCL), U17.4 (SCLK)
/Receiver/EXT_SDA2: J5.A11 (RX2+), R34.2, U16.8 (SDA), U17.5 (SDA)
/Receiver/PULSE2+: J5.A2 (TX1+), U15.8 (Q)
/Receiver/PULSE2-: J5.A3 (TX1-), U15.1 (~Q)
/Receiver/SIPM_BIAS2: J5.A6 (D+), R29.1
/Receiver/V_TRSH: C65.2, U15.4 (-), U16.10 (VOUT)
GND: C43.2, C44.2, C45.2, C46.2, C47.2, C48.2, C49.2, C50.2, C51.1, C52.2, C53.1, C54.1, C55.2, C56.2, C57.2, C58.2, C59.1, C60.2, C63.2, C64.1, C65.1, C66.2, J4.A1 (GND), J4.A12 (GND), J4.B1 (GND), J4.B12 (GND), J4.SH (SHIELD), J5.A1 (GND), J5.A12 (GND), J5.B1 (GND), J5.B12 (GND), J5.SH (SHIELD), R32.2, U12.2 (GND), U12.5 (EPAD), U13.2 (GND), U13.5 (EPAD), U14.1 (GND), U14.3 (GND), U14.4 (GND), U14.6 (GND), U14.8 (GND), U14.9 (GND), U15.2 (GND), U15.3 (VEE), U15.9 (VEE), U15.13 (VEE), U16.4 (~LDAC), U16.5 (GND), U17.2 (GND); also elsewhere on the board
unnamed: C47.1, C48.1, C49.1, R29.2, R30.1
unnamed: C50.1, C51.2, C52.1, D2.1 (K), D2.2 (K), R30.2
unnamed: C55.1, C56.1, C57.1, C58.1, C59.2, FB1.1, L3.2
unnamed: C61.1, FB2.2, U14.7
unnamed: C62.1, D2.3 (A), D2.4 (A), R32.1
unnamed: C62.2, U14.2
unnamed: FB1.2, FB2.1
unnamed: C61.2, R31.2, U15.5 (+)
unnamed: C64.2, U16.9 (VREF)
unnamed: R33.2, U16.3 (~RESET)

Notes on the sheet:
Vcm = Vee + 1.5V
I2C ADDRESS: 1001000
I2C ADDRESS: 1001110
Comparator
